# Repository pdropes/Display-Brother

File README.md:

# Display-Brother
Reverse engineering a display

I had a brother printer, a color display and such, with a dismal flatcable communicating at a speed of +-4MHz... without a logic analyzer, it would be impossible to do anything to understand the protocol. Information on the net is non-existent, however the service manual is always better than nothing.
I got an AL for 200 bucks for this, I still use it.

It took me a long time to make this game, I didn't use any library and the code (Bascom AVR) is in a single file.
With the gathering of information, readings and tests, the files grew, ending up in 3,183 files.
After programming, 33 versions were needed, and now there are no apparent bugs.

These were the reasons why I haven't shared the code and other information yet (besides my pc having crashed), if I'm going to share something, I'd like it to make sense for those who are going to read it, and not a bunch of files.

Both the resolution and the quality reproduced on the display are low, however sufficient for many applications.

I started with an M8515 because it has more IOs, making it possible to connect to a PC's parallel port to exchange information.
All 120ohm resistors were soldered just as a precaution in the tests, there being no need to keep them after confirmation of communications.

The number of connections was reduced to a minimum, sometimes joining some, it was possible to connect it to a common m328 leaving 2 ADC pins available.

A lot of information about commercial displays and mobile phones circulates on the internet, I appreciate whoever recovers unused equipment for other purposes, this was one more challenge and a learning curve, since the expenses far exceed the value of a commercial display.

*Stay creative

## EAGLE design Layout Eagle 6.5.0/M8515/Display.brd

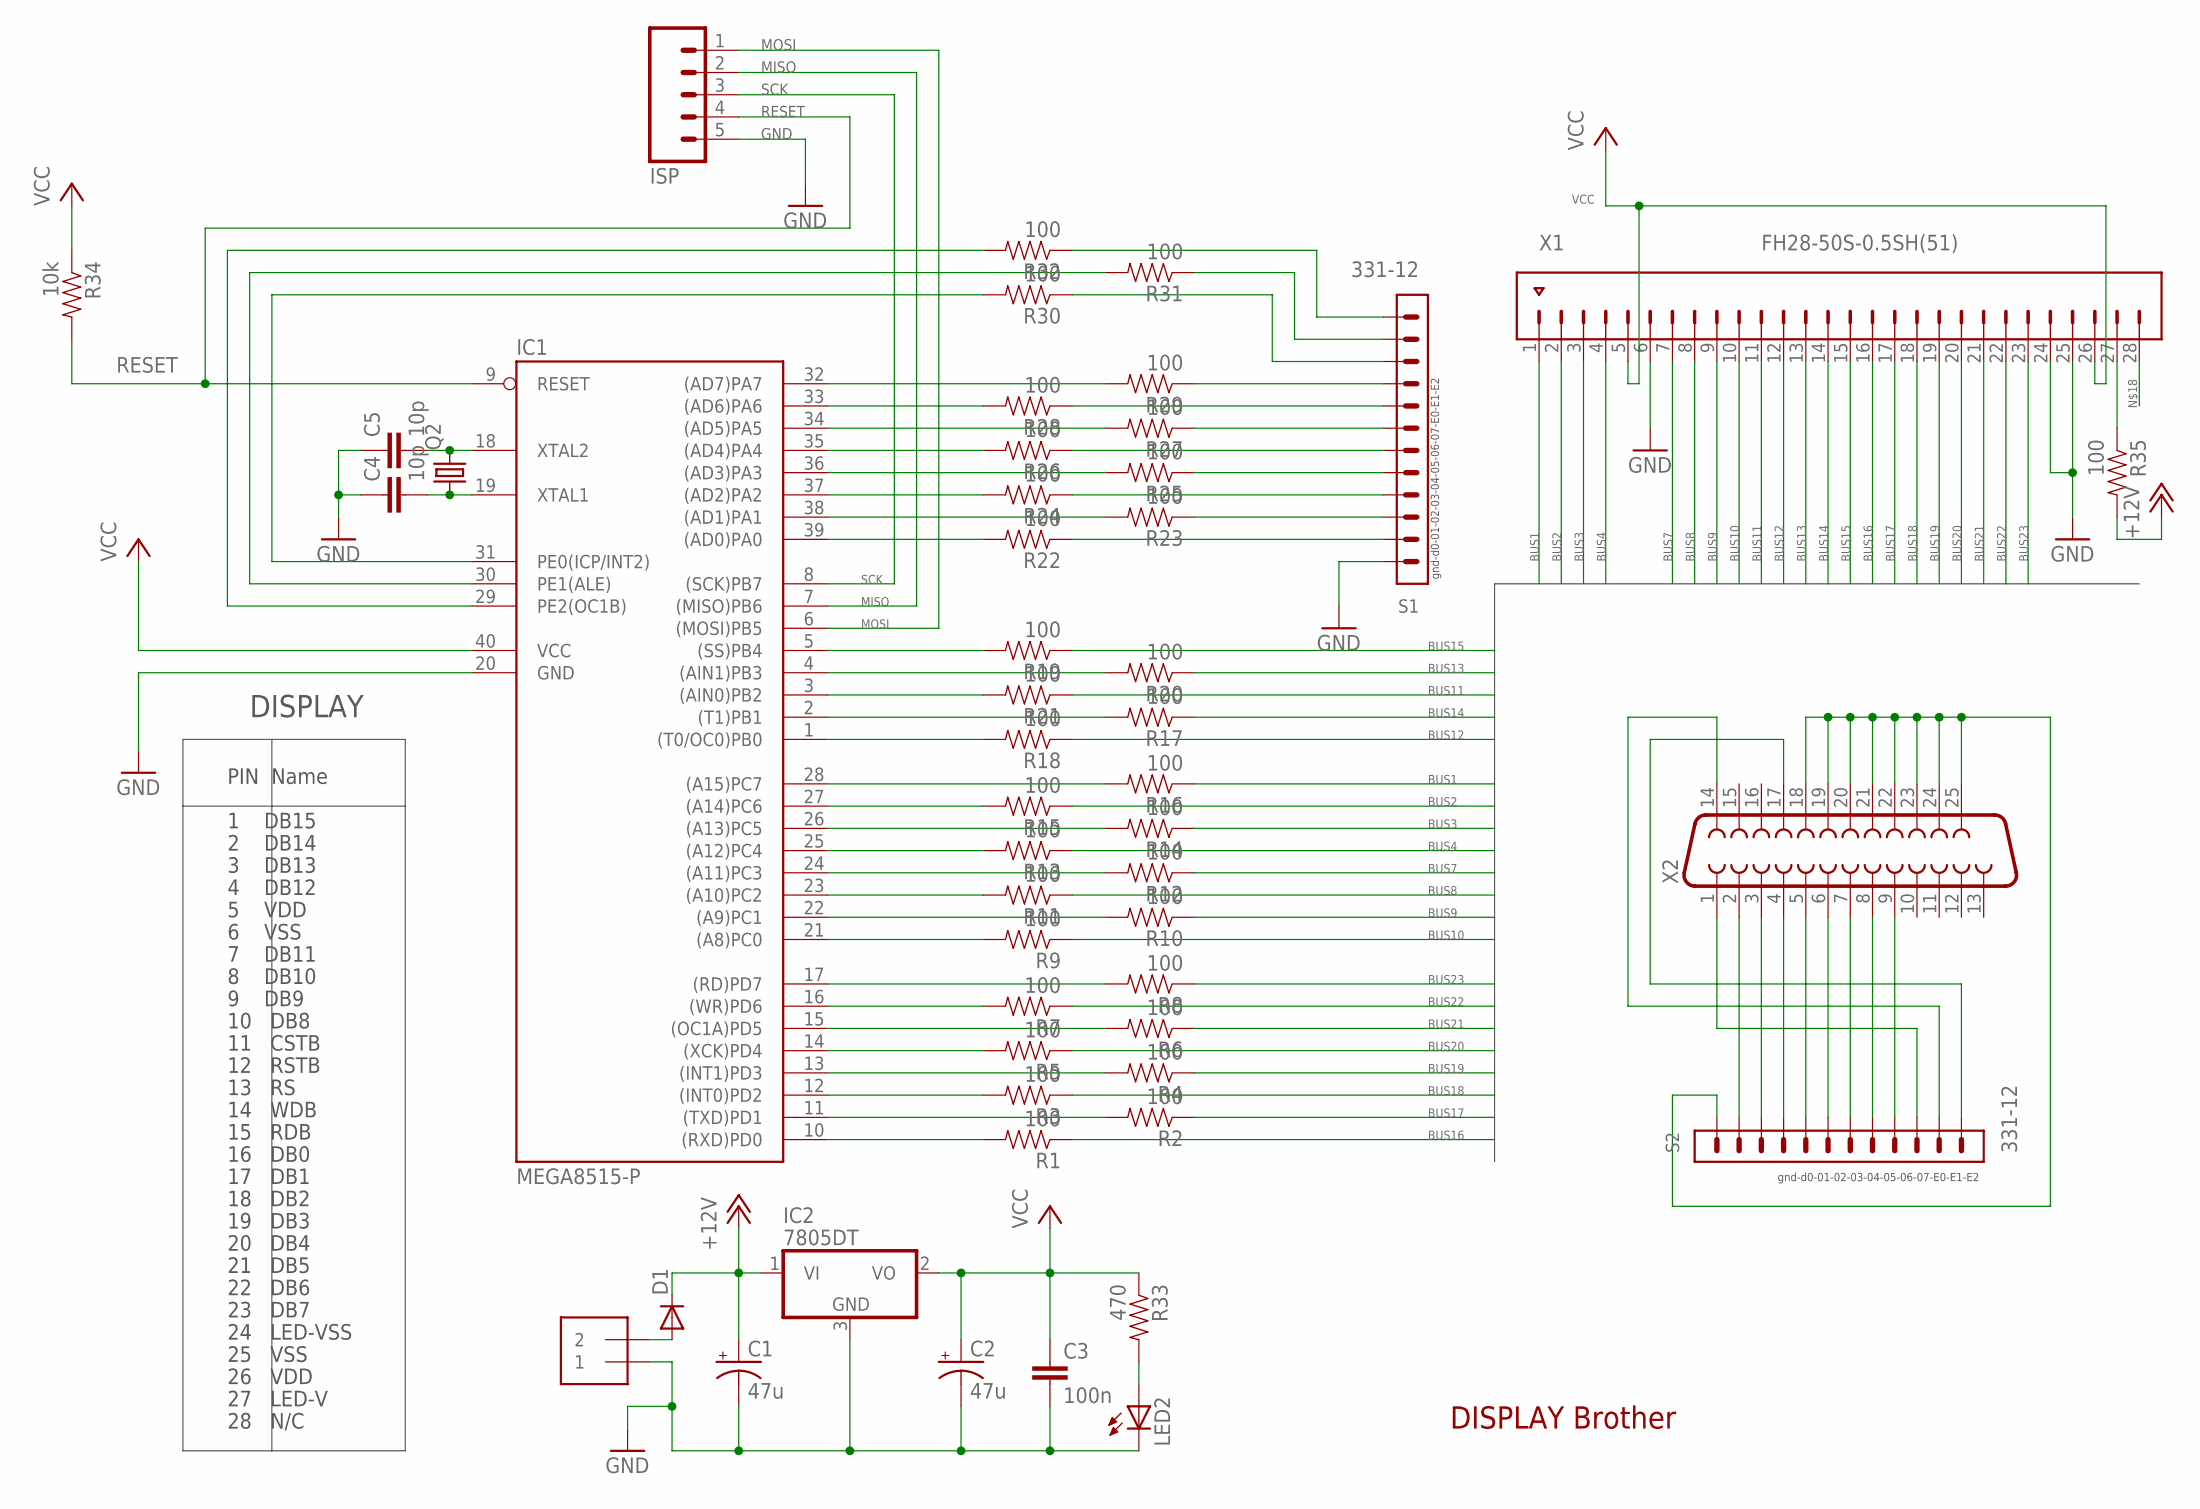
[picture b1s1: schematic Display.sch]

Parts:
C1, C2: 47u; EIA3216-KIT
C3: 100n; 0805
C4, C5: 10p; 0805
D1: DIODESMA-KIT; SMA-DIODE-KIT
IC1: MEGA8515-P; DIL40
IC2: 7805DT; TO252
ISP: M05PTH_LONGPADS; 1X05_LONGPADS
J2: 1X2-3.5MM
LED2: LED3MM
Q2: CRYSTALHC49UP; HC49UP
R1, R2, R3, R4, R5, R6, R7, R8, R9, R10, R11, R12, R13, R14, R15, R16, R17, R18, R19, R20, R21, R22, R23, R24, R25, R26, R27, R28, R29, R30, R31, R32, R35: 100; 0805
R33: 470; 0805
R34: 10k; 0805
S1, S2: 331-12
X1: FH28-50S-0.5SH(51)
X2: F25D

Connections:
+12V: C1.A (+), D1.C, IC2.1 (VI), R35.2
BUS1: R16.1, X1.1
BUS2: R15.1, X1.2
BUS3: R14.1, X1.3
BUS4: R13.1, X1.4
BUS7: R12.1, X1.7
BUS8: R11.1, X1.8
BUS9: R10.1, X1.9
BUS10: R9.1, X1.10
BUS11: R21.1, X1.11
BUS12: R18.1, X1.12
BUS13: R20.1, X1.13
BUS14: R17.1, X1.14
BUS15: R19.1, X1.15
BUS16: R1.1, X1.16
BUS17: R2.1, X1.17
BUS18: R3.1, X1.18
BUS19: R4.1, X1.19
BUS20: R5.1, X1.20
BUS21: R6.1, X1.21
BUS22: R7.1, X1.22
BUS23: R8.1, X1.23
BUS-E0: IC1.31 (PE0(ICP/INT2)), R30.2
BUS-E1: IC1.30 (PE1(ALE)), R31.2
BUS-E2: IC1.29 (PE2(OC1B)), R32.2
GND: C1.C (-), C2.C (-), C3.2, C4.1, C5.1, IC1.20 (GND), IC2.3 (GND), ISP.5, J2.1, LED2.K (C), S1.1, X1.6, X1.24, X1.25
GND3: S2.1, X2.18, X2.19, X2.20, X2.21, X2.22, X2.23, X2.24, X2.25
MISO: IC1.7 ((MISO)PB6), ISP.2
MOSI: IC1.6 ((MOSI)PB5), ISP.1
unnamed: LED2.A, R33.2
unnamed: IC1.10 ((RXD)PD0), R1.2
unnamed: IC1.12 ((INT0)PD2), R3.2
unnamed: IC1.14 ((XCK)PD4), R5.2
unnamed: IC1.16 ((WR)PD6), R7.2
unnamed: IC1.17 ((RD)PD7), R8.2
unnamed: IC1.15 ((OC1A)PD5), R6.2
unnamed: IC1.13 ((INT1)PD3), R4.2
unnamed: IC1.11 ((TXD)PD1), R2.2
unnamed: IC1.28 ((A15)PC7), R16.2
unnamed: IC1.27 ((A14)PC6), R15.2
unnamed: IC1.25 ((A12)PC4), R13.2
unnamed: IC1.23 ((A10)PC2), R11.2
unnamed: IC1.21 ((A8)PC0), R9.2
unnamed: IC1.22 ((A9)PC1), R10.2
unnamed: IC1.24 ((A11)PC3), R12.2
unnamed: IC1.26 ((A13)PC5), R14.2
unnamed: IC1.3 ((AIN0)PB2), R21.2
unnamed: IC1.1 ((T0/OC0)PB0), R18.2
unnamed: IC1.4 ((AIN1)PB3), R20.2
unnamed: C4.2, IC1.19 (XTAL1), Q2.1
unnamed: S2.2, X2.2
unnamed: S2.3, X2.3
unnamed: IC1.2 ((T1)PB1), R17.2
unnamed: S2.4, X2.4
unnamed: S2.5, X2.5
unnamed: S2.6, X2.6
unnamed: S2.7, X2.7
unnamed: IC1.5 ((SS)PB4), R19.2
unnamed: R22.1, S1.2
unnamed: IC1.38 ((AD1)PA1), R23.2
unnamed: R24.1, S1.4
unnamed: S2.8, X2.8
unnamed: IC1.36 ((AD3)PA3), R25.2
unnamed: S2.10, X2.1
unnamed: R26.1, S1.6
unnamed: S2.11, X2.14
unnamed: IC1.34 ((AD5)PA5), R27.2
unnamed: R28.1, S1.8
unnamed: IC1.32 ((AD7)PA7), R29.2
unnamed: IC1.39 ((AD0)PA0), R22.2
unnamed: R23.1, S1.3
unnamed: IC1.37 ((AD2)PA2), R24.2
unnamed: R25.1, S1.5
unnamed: IC1.35 ((AD4)PA4), R26.2
unnamed: R27.1, S1.7
unnamed: IC1.33 ((AD6)PA6), R28.2
unnamed: R29.1, S1.9
unnamed: R30.1, S1.10
unnamed: R32.1, S1.12
unnamed: R31.1, S1.11
unnamed: D1.A, J2.2
unnamed: S2.9, X2.9
unnamed: C5.2, IC1.18 (XTAL2), Q2.2
unnamed: S2.12, X2.17
unnamed: R35.1, X1.27
RESET: IC1.9 (RESET), ISP.4, R34.2
SCK: IC1.8 ((SCK)PB7), ISP.3
VCC: C2.A (+), C3.1, IC1.40 (VCC), IC2.2 (VO), R33.1, R34.1, X1.5, X1.26

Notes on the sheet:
PIN Name
23 DB7
24 LED-VSS
25 VSS
26 VDD
14 WDB
2 DB14
16 DB0
17 DB1
18 DB2
19 DB3
3 DB13
4 DB12
5 VDD
6 VSS
11 CSTB
12 RSTB
13 RS
15 RDB
27 LED-V
1 DB15
7 DB11
8 DB10
9 DB9
10 DB8
28 N/C
22 DB6
21 DB5
20 DB4
DISPLAY
gnd-d0-01-02-03-04-05-06-07-E0-E1-E2
DISPLAY Brother

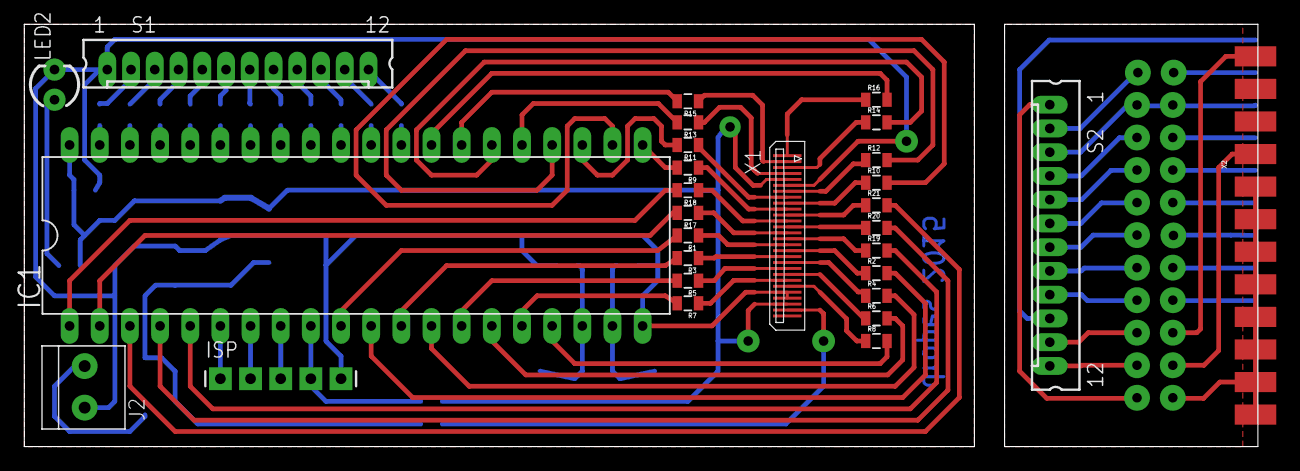
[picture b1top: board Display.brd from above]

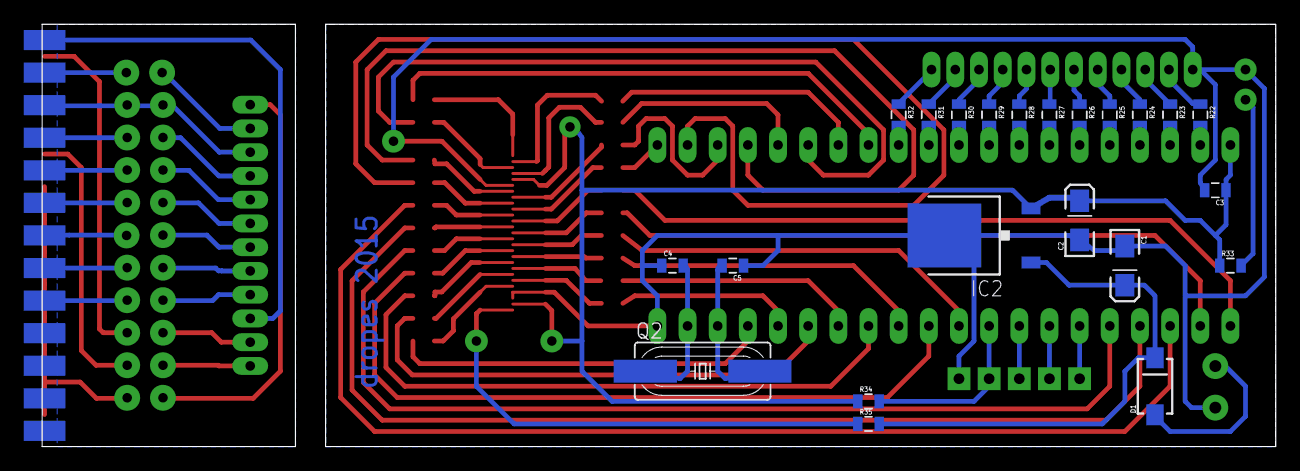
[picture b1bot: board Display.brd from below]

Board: 2 copper layers, 103.9 x 35.6 mm, 51 parts (22 on the bottom side), 88 nets.

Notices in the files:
parts and their libraries:
SparkFun: Licensing: CC v3.0 Share-Alike You are welcome to use this library for commercial purposes.
